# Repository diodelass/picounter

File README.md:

# PiCounter
## Frequency counter for experimental physics using the Raspberry Pi

### Overview
This repository holds schematics and information for the PiCounter, a firmwareless and fairly simple device for accurately measuring
the frequency of an electrical signal using the Raspberry Pi to control data collection. The device has the following features:
- Maximum count rate of up to 40 MHz
- 32-bit count capacity
- Two channels
- AND/OR coincidence mode for cosmic ray detection and similar applications
- Low total cost of manufacture
- Highly stable and accurate quartz-based counting gate timer
- 1/256-second counting time resolution
- Support for arbitrarily long counting times
- Side-mounted serial interface breakout for easy attachment of debug cables
- Support for external clock input

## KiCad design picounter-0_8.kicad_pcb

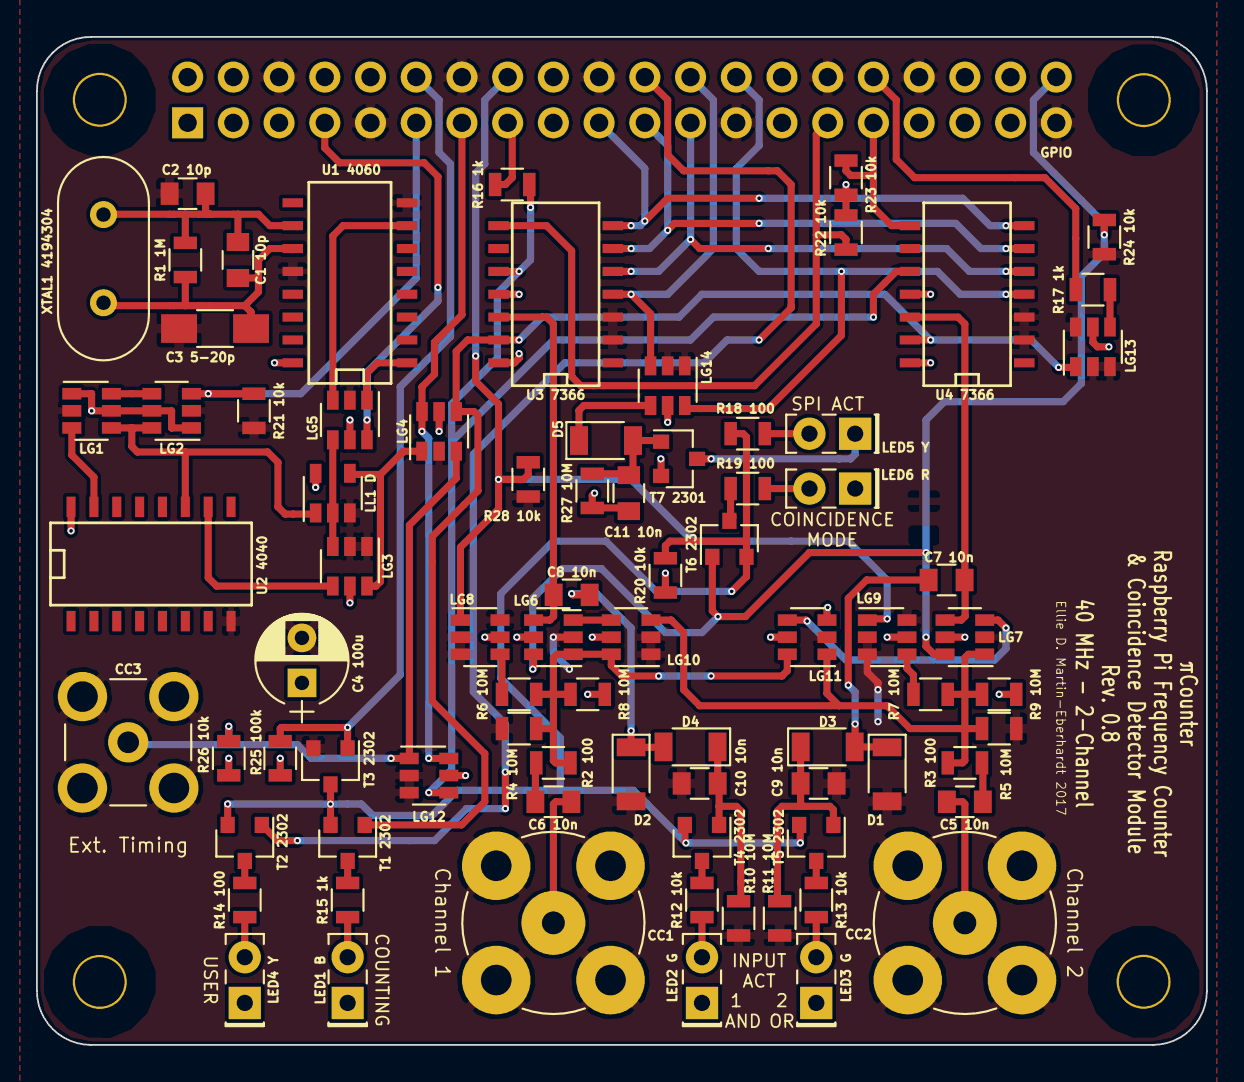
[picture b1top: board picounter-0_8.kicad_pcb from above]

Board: 2 copper layers, 65.0 x 56.0 mm, 85 parts (1 on the bottom side), 2 nets.

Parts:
C1 10p, C2 10p, C5 10n, C6 10n, C7 10n, C8 10n, C9 10n, C10 10n, C11 10n: C_0805
C3 5-20p: C_1206_HandSoldering
C4 100u: CP_Radial_D5.0mm_P2.50mm
CC1, CC2: bnc-ci
CC3: SMB_Straight
D1, D2, D3, D4, D5: D_1206
GPIO: 40HAT; Socket_Strip_Straight_2x20
H1, H2, H3, H4: 3mm_Mounting_Hole; NPTH_3mm_ID
LED1 B, LED2 G, LED3 G, LED4 Y, LED5 Y, LED6 R: LED_Rectangular_W5.0mm_H2.0mm
LG1, LG2, LG3, LG4, LG5, LG6, LG7, LG8, LG9, LG10, LG11, LG12, LG13, LG14: SOT-23-6
LL1 D: SOT-23-5
R1 1M, R2 100, R3 100, R4 10M, R5 10M, R6 10M, R7 10M, R8 10M, R9 10M, R10 10M, R11 10M, R12 10k, R13 10k, R14 100, R15 1k, R16 1k, R17 1k, R18 100, R19 100, R20 10k, R21 10k, R22 10k, R23 10k, R24 10k, R25 100k, R26 10k, R27 10M, R28 10k: R_0805
T1 2302, T2 2302, T3 2302, T4 2302, T5 2302, T6 2302, T7 2301: SOT-23
U1 4060, U2 4040: SO-16-N
U3 7366, U4 7366: SOIC-14_N
XTAL1 4194304: Crystal_HC18-U_Vertical

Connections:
/P5V_HAT: C4 100u.1, C11 10n.1, GPIO.2, GPIO.4, LED1 B.1, LED2 G.1, LED3 G.1, LED4 Y.1, LED6 R.1, LG1.1, LG1.5, LG2.1, LG2.5, LG3.5, LG4.5, LG5.5, LG6.5, LG7.5, LG8.5, LG9.5, LG10.5, LG11.3, LG11.5, LG12.5, LG13.5, LG14.5, LL1 D.5, R8 10M.1, R9 10M.2, R20 10k.1, R22 10k.1, R23 10k.1, R25 100k.2, R26 10k.2, R27 10M.1, T7 2301.2, U1 4060.16, U2 4040.16, U3 7366.11, U3 7366.14, U4 7366.11, U4 7366.14
GND: C2 10p.2, C3 5-20p.2, C4 100u.2, C9 10n.1, C10 10n.1, CC1.2, CC2.2, CC3.2, D1.2, D2.2, GPIO.6, GPIO.9, GPIO.14, GPIO.20, GPIO.25, GPIO.30, GPIO.34, GPIO.39, LG1.2, LG2.2, LG3.1, LG3.2, LG4.2, LG5.2, LG6.2, LG7.2, LG8.2, LG8.3, LG8.6, LG9.2, LG9.3, LG9.6, LG10.1, LG10.2, LG11.2, LG12.2, LG12.3, LG13.2, LG13.3, LG13.6, LG14.1, LG14.2, LL1 D.3, R4 10M.2, R5 10M.2, R10 10M.2, R11 10M.2, R21 10k.1, R24 10k.1, R28 10k.1, T3 2302.2, U1 4060.8, U1 4060.12, U2 4040.8, U3 7366.2, U3 7366.3, U4 7366.2, U4 7366.3

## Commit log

2019-02-16 initial commit: added pcb file, pad assignments, and example python program
2019-02-16 added license
2019-02-16 added footprint/package IDs to pad assignments

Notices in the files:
picounter-0_8.kicad_pcb:
CC-BY 4.0
